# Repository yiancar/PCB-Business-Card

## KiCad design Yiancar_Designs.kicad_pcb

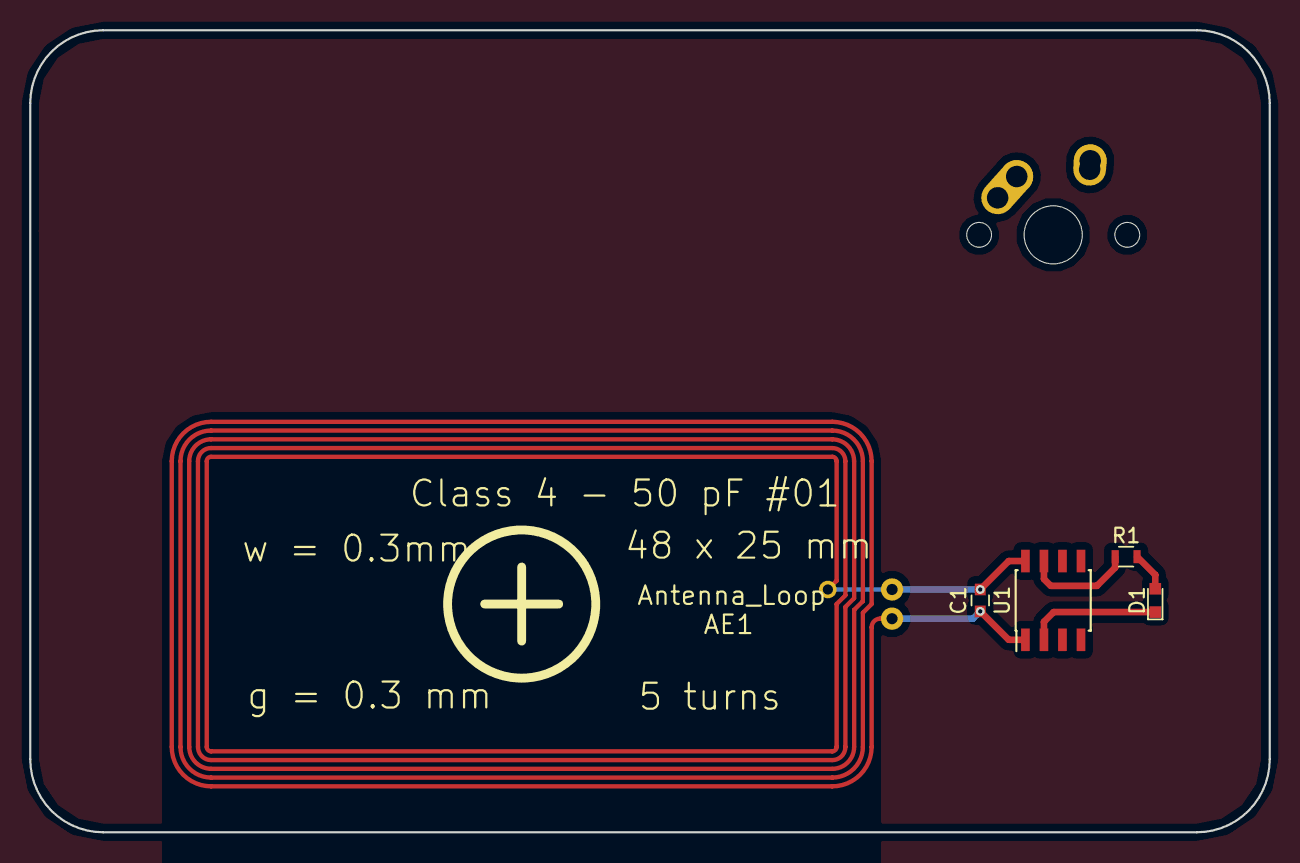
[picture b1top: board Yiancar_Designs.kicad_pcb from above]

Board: 2 copper layers, 85.0 x 55.0 mm, 6 parts (0 on the bottom side), 5 nets.

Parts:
AE1: Antenna_Loop; L_PICC_CLASS4_50PF_01
C1: 130pF; C_0603
D1: 19-217/R6C-AL1M2VY/3T; LED_0603
LOGO: Yiancar_text
R1: 650; R_0603
U1: NT3H2111; SOIC-8_3.9x4.9mm_Pitch1.27mm

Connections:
unnamed: AE1.1, C1.2, U1.1
unnamed: AE1.2, C1.1, U1.8
unnamed: D1.1, U1.2
unnamed: D1.2, R1.2
unnamed: R1.1, U1.7

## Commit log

2018-10-26 test
2019-04-23 Create Icon
